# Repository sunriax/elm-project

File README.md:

# elmProject Diploma work 2016/2017

*The elmProject is a Diplomaproject which has started in the*
*as a small Projet at the HTL-Rankweil. Three Students of the*
*school tryed to develop a system based on a ARM Linux uC and*
*an attached FPGA Device which can be extended over 4 slots on*
*the expanison Headers...*

**Please don´t hesitate to contact us**

## AIMs of the elmProject

**HARDWARE**
1. Build a Mainboard (6-Layer PCB)
	1. with an Xilinx FPGA (Xc7A35T)
	1. with a FIFO (FTDI 240X)
	1. with a 256 MBit SDRAM
	1. with a Programm Flash
	1. with a Bluetooth Module
1. Build a VGA/Sound cart do expand the Mainboard
	1. Soundcard with Wolfson WM8731 Codec
	1. VGA R/G/B output with resistors (Image from FPGA)
1. Build a Analog Board to Measure with the Xilinx XADC
	1. still under development

**SOFTWARE**
1. Run the ACME Arietta G25 uC (Linux)
	1. Compile neccesary Kernel Elements (e.G. Display, ...)
	1. Install and configure neccesary programms (Apache, SSH, ...)
1. Build a Konfiguration for the FPGA (VHDL)
	1. UART communication unit
	1. FIFO communication unit
	1. SDRAM configuration unit
	1. VGA configuration unit
	1. ...
1. Build a Webinterface (PHP/HTML)
	1. To control the whole Mainboard
	1. To Transfer images to the VGA Modul
	1. To Read out analog data
1. Build a Display Software (QT/C++)
	1. Build a Software for the ACME XTerm-01

**DOCUMENTATION**
1. Make a documentation to share the knowledge with other people

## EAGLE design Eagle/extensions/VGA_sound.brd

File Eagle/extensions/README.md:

# elmProject EAGLE files
## VGA/Sound

### Files
1. Library:
		VGA_sound.lbr

1. Schematic:
		VGA_sound.sch
		schematic.pdf

1. Board:
		VGA_sound.brd
		layout.pdf

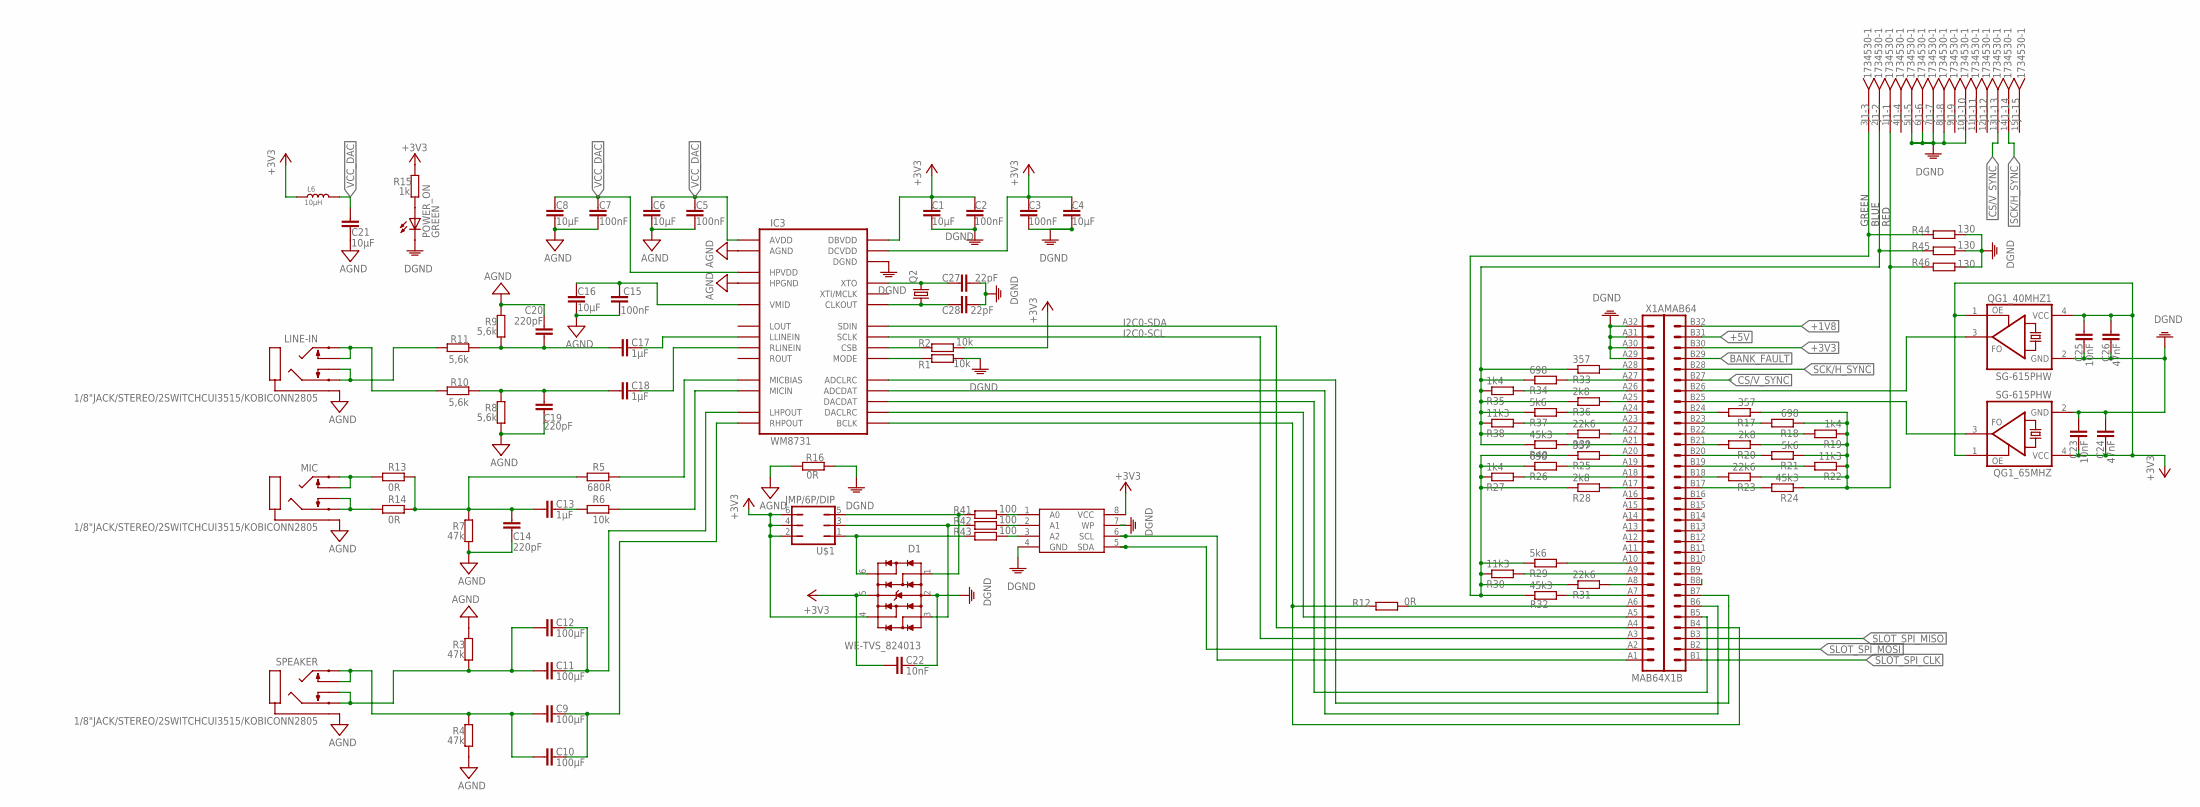
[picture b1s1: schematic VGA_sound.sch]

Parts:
C1, C16, C21: 10µF; C0603
C2, C15: 100nF; C0603
C3, C5, C7: 100nF; C0603K
C4, C6, C8: 10µF; C0603K
C9, C10, C11, C12: 100µF; C1206
C13, C17, C18: 1µF; C0603
C14, C19, C20: 220pF; C0603
C22, C23, C25: 10nF; C0603
C24, C26: 47nF; C0603
C27: 22pF; C0603
C28: 22pF; C0603K
D1: WE-TVS_824013; WE-TVS_SOT23-6L
IC1: EEPROM; SOIC-8
IC3: WM8731; 28-SSOP
J1: 1734530-1; HD15_FEMALE_RIGHT-ANGLE
L6: 10µH; L0805
LINE-IN: 1/8"JACK/STEREO/2SWITCHCUI3515/KOBICONN2805; 1/8"JACK/STEREO/SMT
MIC: 1/8"JACK/STEREO/2SWITCHCUI3515/KOBICONN2805; 1/8"JACK/STEREO/SMT
POWER_ON: GREEN; CHIP-LED0603
Q2: CRYTALSM49; SM49
QG1_40MHZ1, QG1_65MHZ: SG-615PHW; SG-615
R1, R2, R6: 10k; R0603
R3, R4, R7: 47k; R0603
R5: 680R; R0603
R8, R9, R10, R11: 5,6k; R0603
R12, R13, R14, R16: 0R; R0603
R15: 1k; R0603
R17, R25, R33: 357; R0603
R18, R26, R34: 698; R0603
R19, R27, R35: 1k4; R0603
R20, R28, R36: 2k8; R0603
R21, R29, R37: 5k6; R0603
R22, R30, R38: 11k3; R0603
R23, R31, R39: 22k6; R0603
R24, R32, R40: 45k3; R0603
R41, R42, R43: 100; R0603
R44, R45, R46: 130; R0603
SPEAKER: 1/8"JACK/STEREO/2SWITCHCUI3515/KOBICONN2805; 1/8"JACK/STEREO/SMT
U$1: JMP/6P/DIP
X1: MAB64

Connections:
+1V8: X1.B32 (32)
+3V3: C1.2, C2.2, C3.2, C4.2, C22.2, C23.1, C24.1, C25.2, C26.2, D1.4 (3), D1.5 (VDD), IC1.8 (VCC), IC3.P$1 (DBVDD), IC3.P$27 (DCVDD), L6.1, QG1_40MHZ1.1 (OE), QG1_40MHZ1.4 (VCC), QG1_65MHZ.1 (OE), QG1_65MHZ.4 (VCC), R2.2, R15.2, U$1.2, U$1.4, U$1.6, X1.B30 (30)
+5V: X1.B31 (31)
AGND: C5.1, C6.1, C7.1, C8.1, C14.1, C15.1, C16.1, C19.2, C20.1, C21.1, IC3.P$11 (HPGND), IC3.P$15 (AGND), LINE-IN.P$1 (1), MIC.P$1 (1), R3.2, R4.1, R7.1, R8.1, R9.2, R16.2, SPEAKER.P$1 (1)
BANK_FAULT: X1.B29 (29)
CS/V_SYNC: J1.13, X1.B27 (27)
DGND: C1.1, C2.1, C3.1, C4.1, C22.1, C23.2, C24.2, C25.1, C26.1, C27.1, C28.1, D1.2 (GND), IC1.4 (GND), IC1.7 (WP), IC3.P$28 (DGND), J1.5, J1.6, J1.7, J1.8, J1.10, POWER_ON.C, QG1_40MHZ1.2 (GND), QG1_65MHZ.2 (GND), R1.2, R16.1, R44.2, R45.2, R46.2, X1.A29 (29), X1.A30 (30), X1.A31 (31), X1.A32 (32)
I2C0-SCL: IC3.P$24 (SCLK), X1.A3 (3)
I2C0-SDA: IC3.P$23 (SDIN), X1.A4 (4)
unnamed: IC3.P$21 (MODE), R1.1
unnamed: IC3.P$22 (CSB), R2.1
unnamed: C9.1, C10.1, IC3.P$10 (RHPOUT)
unnamed: C27.2, IC3.P$26 (XTO), Q2.2
unnamed: C11.1, C12.1, IC3.P$9 (LHPOUT)
unnamed: C28.2, IC3.P$2 (CLKOUT), Q2.1
unnamed: IC3.P$17 (MICBIAS), R5.2
unnamed: IC3.P$18 (MICIN), R6.2
unnamed: C13.1, R6.1
unnamed: IC3.P$6 (ADCDAT), X1.B6 (6)
unnamed: C17.1, IC3.P$20 (LLINEIN)
unnamed: C17.2, C20.2, R9.1, R11.1
unnamed: C18.1, IC3.P$19 (RLINEIN)
unnamed: C18.2, C19.1, R8.2, R10.1
unnamed: IC1.1 (A0), R41.2
unnamed: IC3.P$4 (DACDAT), X1.B5 (5)
unnamed: LINE-IN.P$2 (3), LINE-IN.P$3 (2), R11.2
unnamed: LINE-IN.P$4 (4), LINE-IN.P$5 (5), R10.2
unnamed: C13.2, C14.2, R5.1, R7.2, R13.2, R14.2
unnamed: MIC.P$4 (4), MIC.P$5 (5), R13.1
unnamed: MIC.P$2 (3), MIC.P$3 (2), R14.1
unnamed: POWER_ON.A, R15.1
unnamed: C11.2, C12.2, R3.1, SPEAKER.P$2 (3), SPEAKER.P$3 (2)
unnamed: IC3.P$7 (ADCLRC), X1.B7 (7)
unnamed: C9.2, C10.2, R4.2, SPEAKER.P$4 (4), SPEAKER.P$5 (5)
unnamed: IC3.P$5 (DACLRC), X1.A5 (5)
unnamed: R12.1, X1.A6 (6)
unnamed: R33.2, X1.A28 (28)
unnamed: R34.2, X1.A27 (27)
unnamed: IC1.6 (SCL), X1.A1 (1)
unnamed: R35.2, X1.A26 (26)
unnamed: R36.2, X1.A25 (25)
unnamed: R38.2, X1.A23 (23)
unnamed: R39.2, X1.A22 (22)
unnamed: R40.2, X1.A21 (21)
unnamed: R25.2, X1.A20 (20)
unnamed: R17.2, X1.B24 (24)
unnamed: R18.2, X1.B23 (23)
unnamed: R19.2, X1.B22 (22)
unnamed: IC3.P$3 (BCLK), R12.2, X1.B4 (4)
unnamed: R20.2, X1.B21 (21)
unnamed: R21.2, X1.B20 (20)
unnamed: R22.2, X1.B19 (19)
unnamed: R23.2, X1.B18 (18)
unnamed: QG1_65MHZ.3 (FO), X1.B25 (25)
unnamed: R24.2, X1.B17 (17)
unnamed: R26.2, X1.A19 (19)
unnamed: IC1.2 (A1), R42.2
unnamed: IC1.3 (A2), R43.2
unnamed: J1.3, R25.1, R26.1, R27.1, R28.1, R29.1, R30.1, R31.1, R32.1, R44.1
unnamed: R27.2, X1.A18 (18)
unnamed: D1.1, R41.1, U$1.5
unnamed: D1.3 (2), R42.1, U$1.3
unnamed: R28.2, X1.A17 (17)
unnamed: D1.6 (4), R43.1, U$1.1
unnamed: QG1_40MHZ1.3 (FO), X1.B26 (26)
unnamed: R37.2, X1.A24 (24)
unnamed: R29.2, X1.A10 (10)
unnamed: R32.2, X1.A7 (7)
unnamed: R31.2, X1.A8 (8)
unnamed: R30.2, X1.A9 (9)
unnamed: J1.1, R17.1, R18.1, R19.1, R20.1, R21.1, R22.1, R23.1, R24.1, R46.1
unnamed: IC1.5 (SDA), X1.A2 (2)
unnamed: J1.2, R33.1, R34.1, R35.1, R36.1, R37.1, R38.1, R39.1, R40.1, R45.1
unnamed: C15.2, C16.2, IC3.P$16 (VMID)
SCK/H_SYNC: J1.14, X1.B28 (28)
SLOT_SPI_CLK: X1.B1 (1)
SLOT_SPI_MISO: X1.B3 (3)
SLOT_SPI_MOSI: X1.B2 (2)
VCC_DAC: C5.2, C6.2, C7.2, C8.2, C21.2, IC3.P$8 (HPVDD), IC3.P$14 (AVDD), L6.2

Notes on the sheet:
RED
GREEN
BLUE

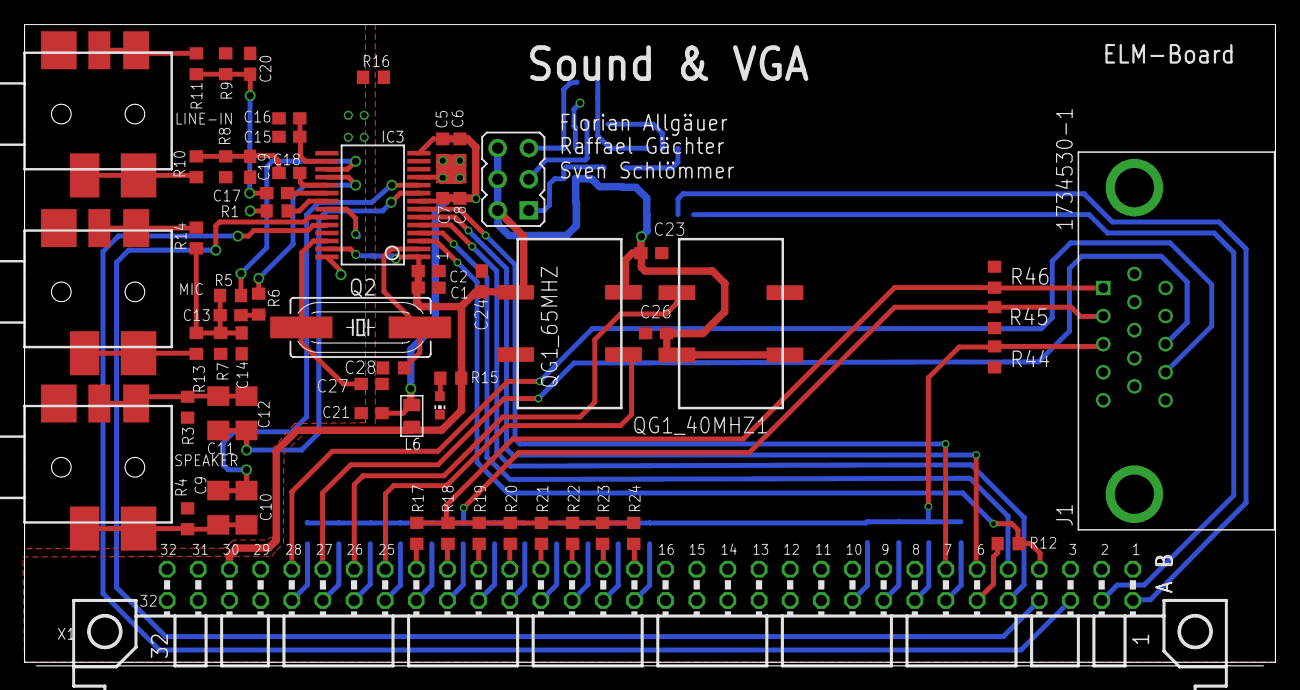
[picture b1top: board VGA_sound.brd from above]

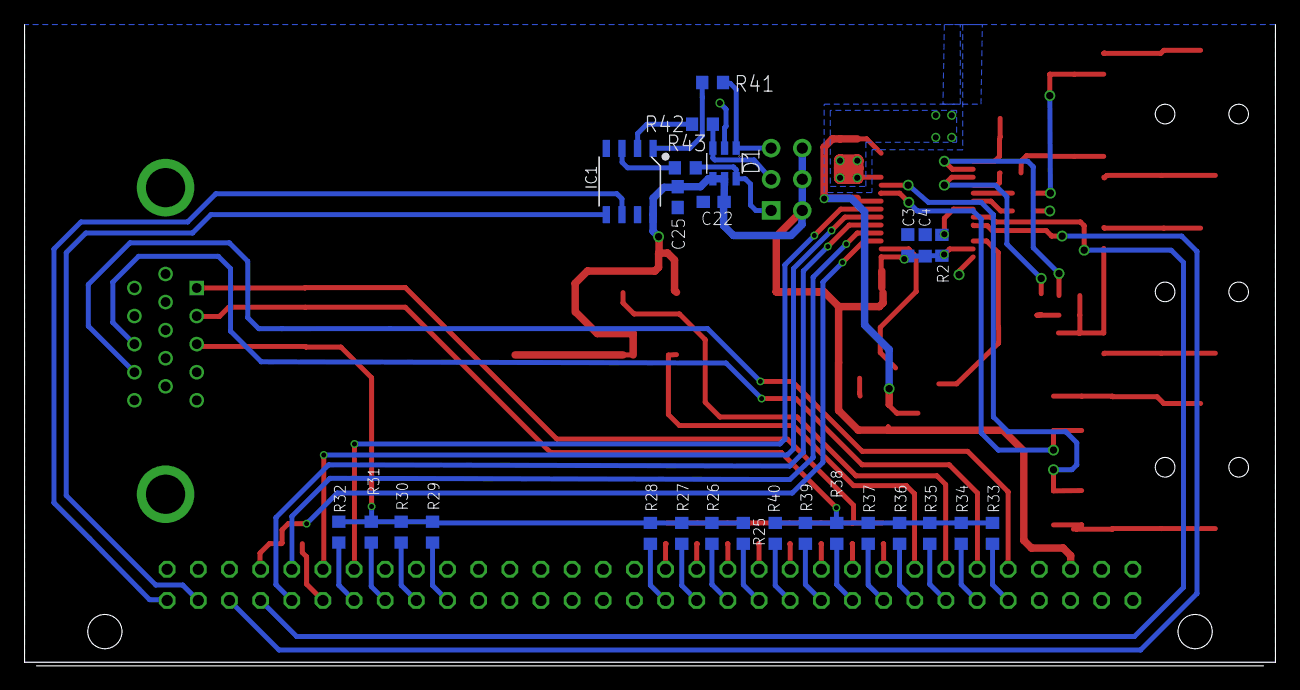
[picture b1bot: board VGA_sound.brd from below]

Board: 2 copper layers, 102.0 x 52.3 mm, 88 parts (26 on the bottom side), 73 nets.

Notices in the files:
parts and their libraries:
Board_to_Board_Connectors_rev15d: Copyright: Würth Elektronik
vga: Creative Commons Attribution-ShareAlike 3.0 Unported (CC BY-SA 3.0), http://creativecommons.org/licenses/by-sa/3.0/.
